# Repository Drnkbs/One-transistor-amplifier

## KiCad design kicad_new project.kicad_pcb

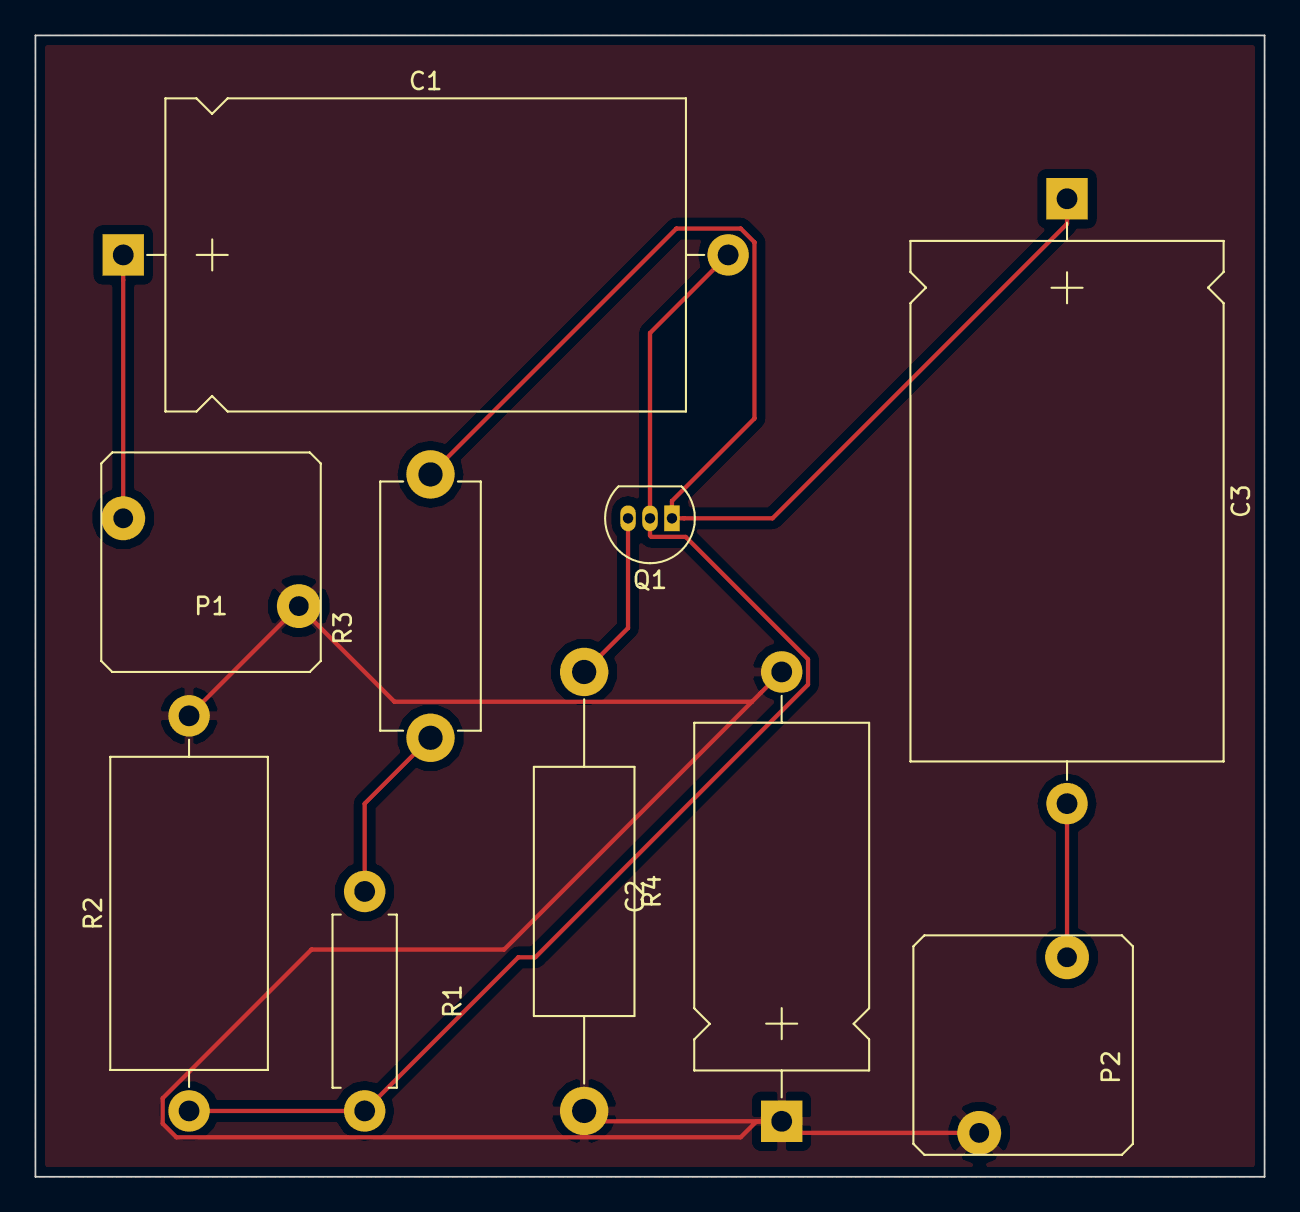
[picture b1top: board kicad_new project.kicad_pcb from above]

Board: 2 copper layers, 71.1 x 66.0 mm, 10 parts (0 on the bottom side), 7 nets.

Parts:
C1, C3: 20uF; CP_Axial_L30.0mm_D18.0mm_P35.00mm_Horizontal
C2: 50uF; CP_Axial_L20.0mm_D10.0mm_P26.00mm_Horizontal
P1: Signal_In; SW_PUSH
P2: Signal_Out; SW_PUSH
Q1: BC548; TO-92_Inline_Narrow_Oval
R1: 22k; R_Axial_DIN0411_L9.9mm_D3.6mm_P12.70mm_Horizontal
R2: 6.8k; R_Axial_DIN0918_L18.0mm_D9.0mm_P22.86mm_Horizontal
R3: 4.7k; R_Axial_DIN0614_L14.3mm_D5.7mm_P15.24mm_Horizontal
R4: 1.8k; R_Axial_DIN0614_L14.3mm_D5.7mm_P25.40mm_Horizontal

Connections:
+12V: R1.1, R3.1
GND: C2.1, C2.2, P1.1, P2.2, R2.2, R4.2
unnamed: C1.1, P1.2
unnamed: C1.2, Q1.2, R1.2, R2.1
unnamed: C3.1, Q1.1, R3.2
unnamed: C3.2, P2.1
unnamed: Q1.3, R4.1

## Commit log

2017-03-25 One Transistör Amp
2017-05-27 One _transistor _amplifier
